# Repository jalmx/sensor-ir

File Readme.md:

# Sensor IR with LM358

Project designed with [KiCAD](https://www.kicad.org)

## Details about develop

[Calculate](Calculator/Calculator.pdf)

## Bills of Materials

- 1 LM358N
- 2 2N2222
- Led Infrared IR333
- Phototransistor PT331C
- Resistors 10k, 333k,5.6k, 1k
- 1 Potentiometer 10k
- 1 Relay 5VDC 

## Download

Download the schematic diagram [here](dist/sensonr_ir.pdf)

## Photos

## Schematic

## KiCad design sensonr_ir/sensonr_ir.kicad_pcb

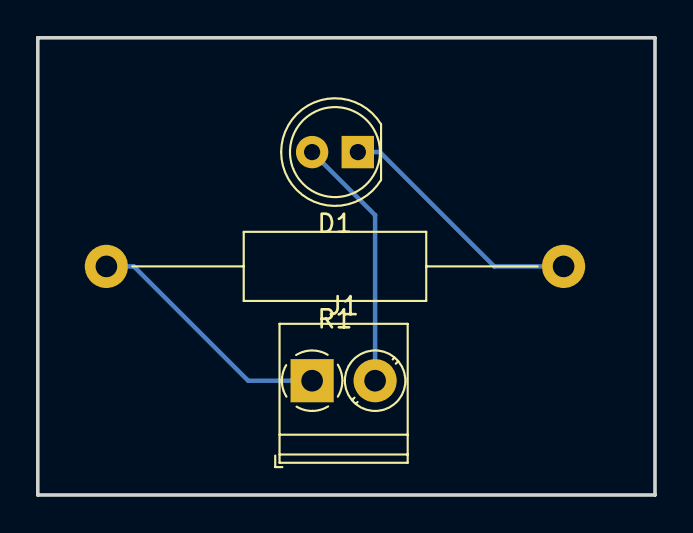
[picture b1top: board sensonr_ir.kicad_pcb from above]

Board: 2 copper layers, 34.3 x 25.4 mm, 3 parts (0 on the bottom side), 3 nets.

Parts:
D1: LED; LED_D5.0mm
J1: Conn_01x02; TerminalBlock_Phoenix_PT-1,5-2-3.5-H_1x02_P3.50mm_Horizontal
R1: 330; R_Axial_DIN0411_L9.9mm_D3.6mm_P25.40mm_Horizontal

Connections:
GND: J1.1, R1.2
unnamed: D1.1, R1.1
VCC: D1.2, J1.2

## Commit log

2018-04-01 Readme
2018-04-01 dist
2018-04-01 photos
2018-04-01 calculator
2022-03-13 fix: README
